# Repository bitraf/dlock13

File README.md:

# dlock13

Breakout design (in EAGLE) and source code for our door lock actuator, running on a Raspberry PI(1).
Communication with the lock happens over [MQTT](https://en.wikipedia.org/wiki/MQTT).
Does not contain user interface, check [door-web](https://github.com/bitraf/door-web) for that.

## MQTT interface

To open the door, send the *number of seconds to open* to:

    /bitraf/door/$door_id/open  # Ex: 20

On success, will output values:

    /bitraf/door/$door_id/isopen # Ex: true/false
    /bitraf/door/$door_id/openuntil # Unix timestamp when door will lock again. Ex: 1495469392

On error, will send a string with an error message:

    /bitraf/door/$door_id/error # Ex: "Time to open is negative"

Where `$door_id` is for instance `2floor`, `frontdoor`, `4floor`.
The `/bitraf/door/` prefix is configurable, can be set to `/mysystem/doorlocks`.

## Code

At [dlock13-msgflo/dlock13.cpp](./dlock13-msgflo/dlock13.cpp).

Impementation is in C++11, using [msgflo-cpp](https://github.com/msgflo/msgflo-cpp). 

## Python API

Also provided is a simple Python module which will handle checking the MQTT messages
being sent out on success/error.

Installing

    pip install dlock13

A command-line tool is included

    dlock13-open /bitraf/door/$door_id 60

For how to use programatically, use [dlock13-open](./dlock13-open) as example code.

## Board

The board has two MOSFETS for driving standard electronic locks.
Expansion for two inputs also exists.

Single-sided board with through-hole components, can easily be CNC milled or etched.

### Pinout

    # Function | Connector pin |  BCM SoC pin |  WiringPi pin  |
    ===
    mosfet1    |     19        |   10         |  12
    mosfet2    |     2         |   11         |  14

BCM SoC pin is the on used for `/sys/class/gpio/gpioNN` and similar.

## Deployment

A systemd service template is normally used to each doorlock: [dlock13@.service](dlock13-msgflo/dlock13@.service).

    systemctl status dlock13@2floor

The following environment variables are used. They can be specified in `/etc/dlock13/$door_id.conf`.

* `MSGFLO_BROKER` - the MQTT broker connection details. Ex: `mqtt://user:password@mqtt.example.net`
* `DLOCK13_PIN` - the GPIO pin number to use. Ex: `11`

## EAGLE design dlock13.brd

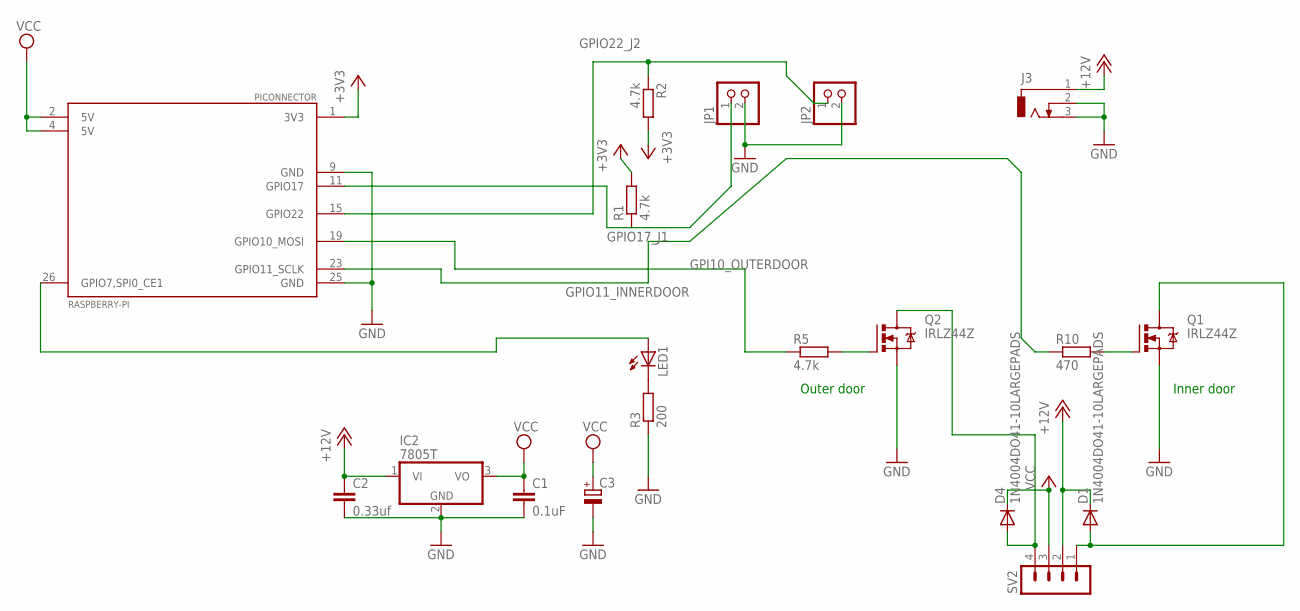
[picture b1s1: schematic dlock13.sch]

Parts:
C1: 0.1uF; C2.5-3
C2: 0.33uf; C2.5-3
C3: CPOL-EUE1,8-4LARGEPADS; E1,8-4
D1, D4: 1N4004DO41-10LARGEPADS; DO41-10
IC2: 7805T; TO220H
J3: DCJ0303DCJ0303LARGEPADS; DCJ0303
JP1: PINHD-1X2; 1X02
JP2: PINHD-1X21X02LARGEPADS; 1X02
LED1: LEDLED5MMLARGEPADS; LED5MM
PICONNECTOR: RASPBERRY-PI; RASPBERRY-PI_REV1
Q1, Q2: IRLZ44Z; TO220BH
R1, R2, R5: 4.7k; 0207/10
R3: 200; 0207/10
R10: 470; 0207/10
SV2: MA04-1MA04-1LARGEPADS; MA04-1

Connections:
+3V3: PICONNECTOR.1 (3V3), R1.2, R2.2
+12V: C2.1, D1.C, IC2.1 (VI), J3.1, SV2.2
GND: C1.2, C2.2, C3.-, IC2.2 (GND), J3.2, J3.3, JP1.2, JP2.2, PICONNECTOR.9 (GND), PICONNECTOR.25 (GND), Q1.S, Q2.S, R3.1
GPI10_OUTERDOOR: PICONNECTOR.19 (GPIO10_MOSI), R5.1
GPIO11_INNERDOOR: PICONNECTOR.23 (GPIO11_SCLK), R10.1
GPIO17_J1: JP1.1, PICONNECTOR.11 (GPIO17), R1.1
GPIO22_J2: JP2.1, PICONNECTOR.15 (GPIO22), R2.1
unnamed: D1.A, Q1.D, SV2.1
unnamed: Q1.G, R10.2
unnamed: Q2.G, R5.2
unnamed: LED1.K (C), R3.2
unnamed: LED1.A, PICONNECTOR.26 (GPIO7,SPI0_CE1)
unnamed: D4.A, Q2.D, SV2.4
VCC: C1.1, C3.+, D4.C, IC2.3 (VO), PICONNECTOR.2 (5V), PICONNECTOR.4 (5V), SV2.3

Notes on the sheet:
Inner door
Outer door

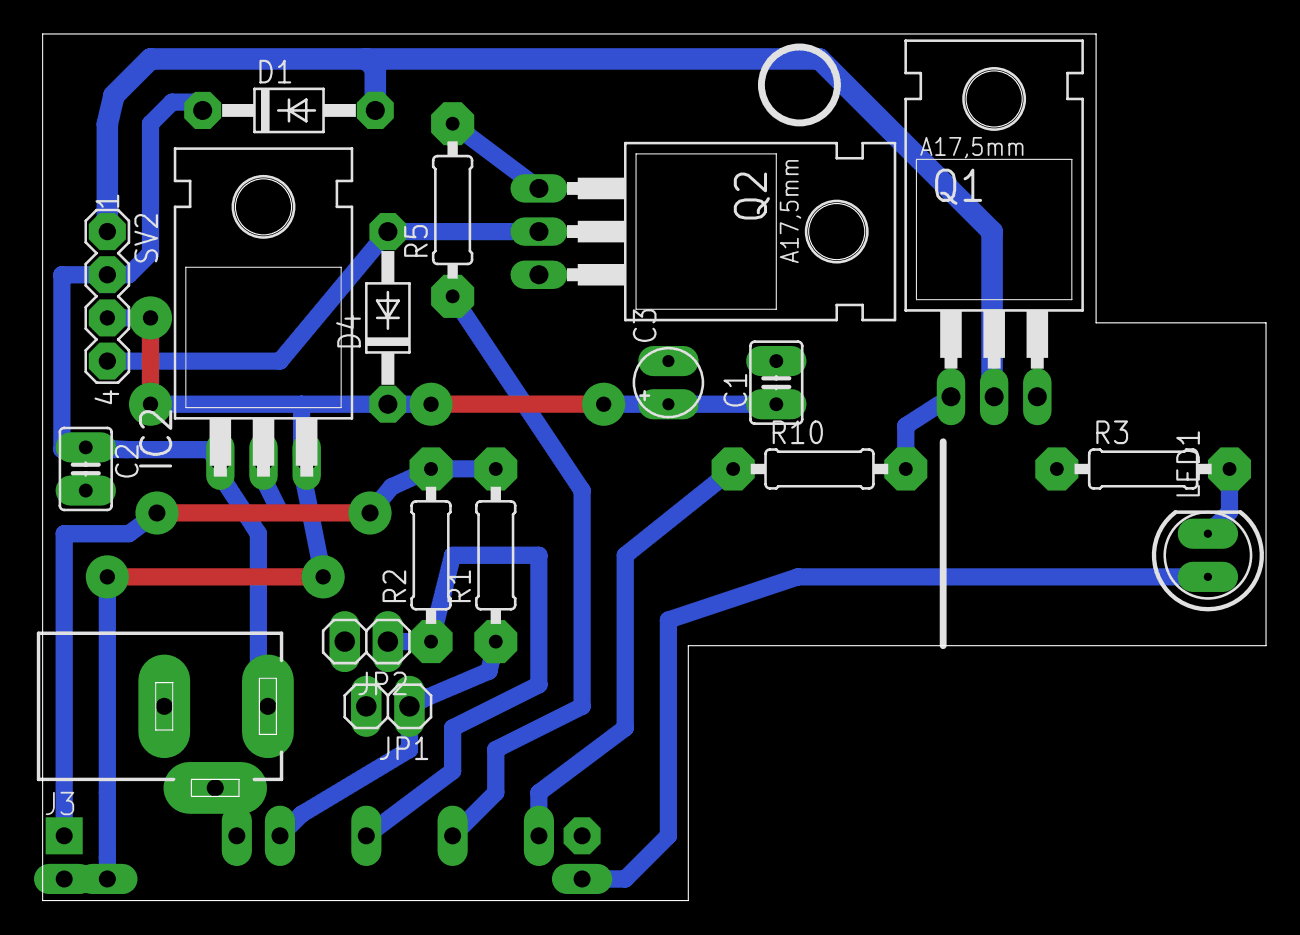
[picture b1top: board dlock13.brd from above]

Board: 2 copper layers, 72.0 x 51.0 mm, 19 parts (0 on the bottom side), 14 nets.

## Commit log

2013-06-28 Initial commit of unfinished board.
2013-06-28 Updated.
2013-08-13 Add vidarkr's changes. Produced and In use.
2013-08-14 Add source code for unlocking door.
2016-03-22 add readme
2016-03-22 add md suffix
2016-04-08 o Adding mqtt-based unlocker.
2016-04-09 mqtt: Improved publisher and subscriber.
2016-04-09 mqtt: Nits.
2016-04-10 Update dimension to follow board edge
2016-04-10 Remove unlock binary
2016-04-10 mqtt: Substitute .service files during make install
2016-04-10 mqtt: Automatically install .service file
2016-04-10 mqtt: Fix setting DOOR variable for makefile
2016-04-10 mqtt subscriber: Remove explicit clientid and while loop
    Fixes not getting all the messages
2016-04-10 README: More info, link to door-web
2016-04-10 README: Add picture
    Says more than 1k words ;)
2016-04-11 mqtt subscriber: Wait for network-online.target
    Otherwise will retry 5 times and then enter failed state
2016-08-01 Install MsgFlo
2016-08-01 Add msgflo participant declaration and graph
2016-08-01 MsgFlo: Install MQTT driver lib
2016-08-01 Working MsgFlo graph for door system using a Diller-based button
2016-08-01 Add a TODO
2016-08-01 Fix the TODO
2016-08-01 [APIBREAK]Change all topics to have /bitraf prefix
2016-08-01 Update TODO
2016-08-01 MsgFlo: Declare webui, sending to open both doors
2016-08-01 MQTT: Add new memberinfo
2016-08-01 mqtt: Default broker to mqtt.bitraf.no
2016-08-01 mqtt: Skeleton code for showing messages on infodisplay/TV
2016-08-01 mqtt: Update TV with non-hardcoded url
2016-08-01 mqtt: Urlencode TV message
2016-08-01 mqtt: Fix problem with newline in TV messages
2016-08-01 mqtt: Fix unable to authenticate to Xorg from service
2016-08-01 mqtt: Also include the ShowMessage
2016-08-02 mqtt: Add a participant for formatting a welcome message
2016-08-02 Makefile: Don't automatically run door service on install
2016-08-02 Move general MQTT things to bitraf-iot
    https://github.com/bitraf/bitraf-iot
2016-08-03 WIP: MsgFlo-based implementation of unlocking.
2016-08-03 WIP: Updating to latest API.
2016-10-10 dlock13-msgflo: Update to latest msgflo-cpp, skeleton implementation
    Compiles but has several things not implemented yet
2016-10-10 dlock-msgflo: Basic working implementation
    Needs tests
2016-10-10 dlock-msgflo: Make queue names compatible
2016-10-10 dlock13-msgflo: Add tests using fbp-spec
2016-10-10 .gitignore: Ignore CMake related files
2016-10-10 Travis: Add inital file
2016-10-10 Travis: Install & run Mosquitto
2016-10-10 Travis: Try fix working directory
2016-10-10 Travis: Try fix working directory again
2016-10-11 Travis: Use build.sh script
2016-10-11 Travis: Try to fix cmake 3.5 lookup
2016-10-11 dlock13-msgflo: Fix wrong hack in build.sh
2016-10-11 msgflo-cpp: Update with libev fix
2016-10-11 msgflo: Require 0.9.1, with some fbp-spec fixes
2016-10-11 fbp-spec: Bump with a fix
2016-10-11 Travis: Enable DEBUG for fbp-spec
    Is hanging...
2016-10-11 dlock13-msgflo: Fix wrong path to executable
2016-10-11 Revert "Travis: Enable DEBUG for fbp-spec"
    This reverts commit 644c553fc430899ce289c49083eb1b34a6bb06e8.
2016-10-11 README: Document GPIO pins
2016-10-11 README: Add picture of schematic
2016-10-12 build.sh: Specify number for -j, avoids infinite spawns and OOM
2016-10-12 CMake: Allow version 3.0+
    Raspbian and similar does not have 3.5+
2016-10-12 CMake: Explicitly configure C++11
    Fixes build with GCC 4.9
2016-10-12 msgflo-cpp: Update to latest, with RPi fixes
2016-10-12 dlock13-msgflo: Make prefix configurable
2016-10-12 dlock13-msgflo: Include role name in label
2016-10-12 dlock13-msgflo: Lock door on startup
2016-10-12 msgflo-cpp: Update to version with configurable debug
2016-10-12 Add initial systemd service file
2016-10-12 Setup GPIO in systemd service
2016-10-12 Make systemd service a template
2016-10-12 Fix systemd service to be configurable
2017-04-07 Making build.sh a bit more bullet proof, always pull submodules to make sure that we have all dependencies. It'll only take a second anyway.
2017-04-07 Trying to improve stability issues: o Enabling debugging in msgflo. o Show the given configuration values, useful for looking back in the logs. o Setting RestartSec=3 to get a bit more delay after ea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
2017-05-19 Fix warning
    debugOutput() returns void in currently used version
2017-05-22 Remove unused MQTT shell code
    Since 1 year back we are using dlock13-msgflo, in C++
2017-05-22 README: Update documentation
2017-05-22 Remove unused WiringPi code
    Not used for over 1 year
2017-05-22 msgflo-cpp: Update to 0.1.0
2017-06-07 Skeleton Python API for unlocking over MQTT
2017-06-07 PythonApi: Happy case passing
    When running the lock code manually
    touch first.gpio
    MSGFLO_BROKER=mqtt://localhost ./dlock13-msgflo/build/dlock13 first first.gpio test/door/
2017-06-07 gitignore .pyc files
2017-06-07 Python API: Basic sad cases covered
2017-06-07 Python API: Return error message from MQTT in exception
    Nicer than just getting a generic Timeout
2017-06-07 Travis: Also run nosetests
2017-06-07 tests: Check Python API in a Flask app
2017-06-07 Travis: Install requirements, try to fix nose executable name
2017-06-07 Travis: Try to install nose manually
2017-06-07 Travis: Remove debug
2017-06-07 Travis: Autodeploy Python package to PyPi
2017-06-07 Bump
2017-06-07 Python: Rename Doorlock to Opener
    Since its actually not the lock, and can in fact open multiple configured doors
2017-06-07 dlock13-open: Tiny CLI tool for opening a door
    Uses the Python API, checking for success/errors
2017-06-07 Travis: Try fix PyPi deploy
2017-06-28 msgflo-cpp: Update to 0.2.1
    Fixes periodic discovery message and using username/password
2017-06-28 Fix too eager postcondition
    When door was recently opened, the currentState.openUntil will
    be a bit in the future. Thus we cannot assume that we will extend
    it by at least openSeconds.
    The invariant only holds wrt to current time
2017-11-06 Travis: Update to Node.js 8
2017-11-06 Travis: Specify Trusty
2017-11-06 Travis: Remove old PPAs
    Hopefully not needed on Trusty
2017-11-06 Travis: Install libev
2017-11-06 tests: Enable happy case check
2017-11-06 Setup Docker-based build for RPi3
2017-11-06 build.sh: Don't update submodules
    This is responsibility of code outside
2017-11-06 Travis: Run Docker for RPi and collect result
2017-11-06 Travis: Upload build to Github Releases
2017-11-06 Travis: Fix build matrix declaration
2017-11-06 Travis: Require Docker service
2017-11-06 Travis: Build for Docker first
2017-11-06 Travis: Setup envvars together with build matrix
2017-11-09 NPM: Update msgflo to 0.11
2017-11-09 NPM: Update fbp-spec to 0.4.xy
2020-06-09 document how to make a base image
2020-06-09 fix formatting
2020-06-09 more formatting fixes
2020-06-09 final formatting fixes
2020-06-09 base image - document where it is and how to use it
2020-06-09 fix spelling
2020-06-10 correct link to base image
2020-10-01 correct filename of base image in example
2020-10-01 chnage password
